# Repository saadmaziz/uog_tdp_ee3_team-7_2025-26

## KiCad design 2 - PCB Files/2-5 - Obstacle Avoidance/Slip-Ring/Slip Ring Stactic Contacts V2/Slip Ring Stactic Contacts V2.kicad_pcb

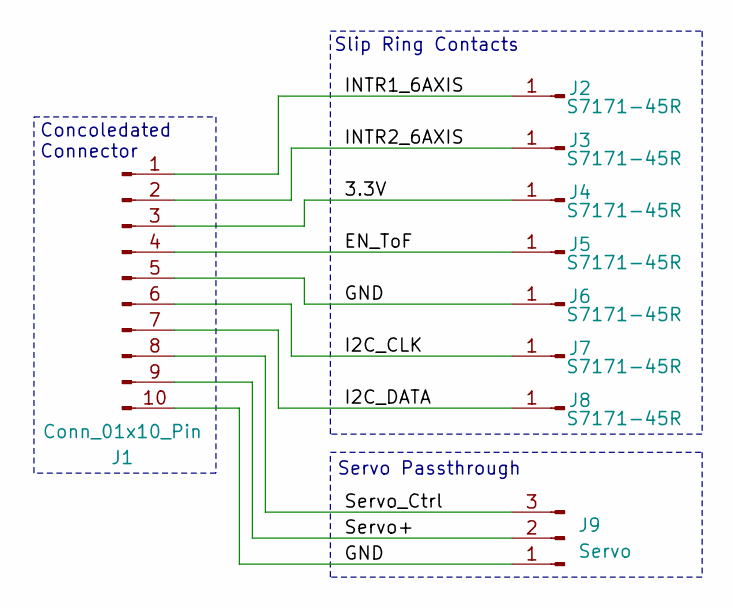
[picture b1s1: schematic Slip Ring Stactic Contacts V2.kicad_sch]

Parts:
J1: Conn_01x10_Pin; Molex_KK-254_AE-6410-10A_1x10_P2.54mm_Vertical
J2, J3, J4, J5, J6, J7, J8: S7171-45R; S717145R
J9: Servo; PinHeader_1x03_P2.54mm_Vertical

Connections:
/3.3V: J1.3, J4.1
/EN_ToF: J1.4, J5.1
/GND: J1.5, J1.10, J6.1, J9.1
/I2C_CLK: J1.6, J7.1
/I2C_DATA: J1.7, J8.1
/INTR1_6AXIS: J1.1, J2.1
/INTR2_6AXIS: J1.2, J3.1
/Servo+: J1.9, J9.2
/Servo_Ctrl: J1.8, J9.3

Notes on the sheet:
Slip Ring Contacts
Servo Passthrough
Concoledated Connector

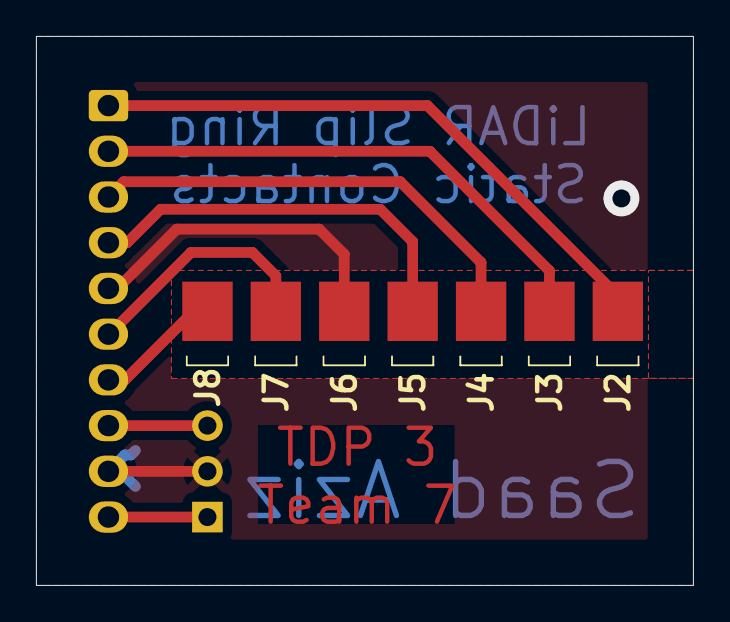
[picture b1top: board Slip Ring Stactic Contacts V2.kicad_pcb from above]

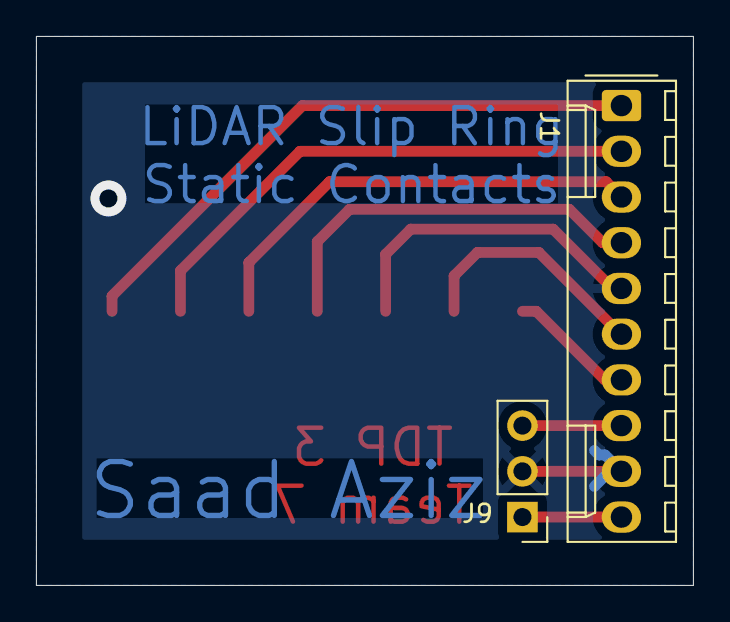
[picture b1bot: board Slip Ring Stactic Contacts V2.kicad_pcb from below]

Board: 2 copper layers, 36.5 x 30.5 mm, 9 parts (2 on the bottom side), 9 nets.

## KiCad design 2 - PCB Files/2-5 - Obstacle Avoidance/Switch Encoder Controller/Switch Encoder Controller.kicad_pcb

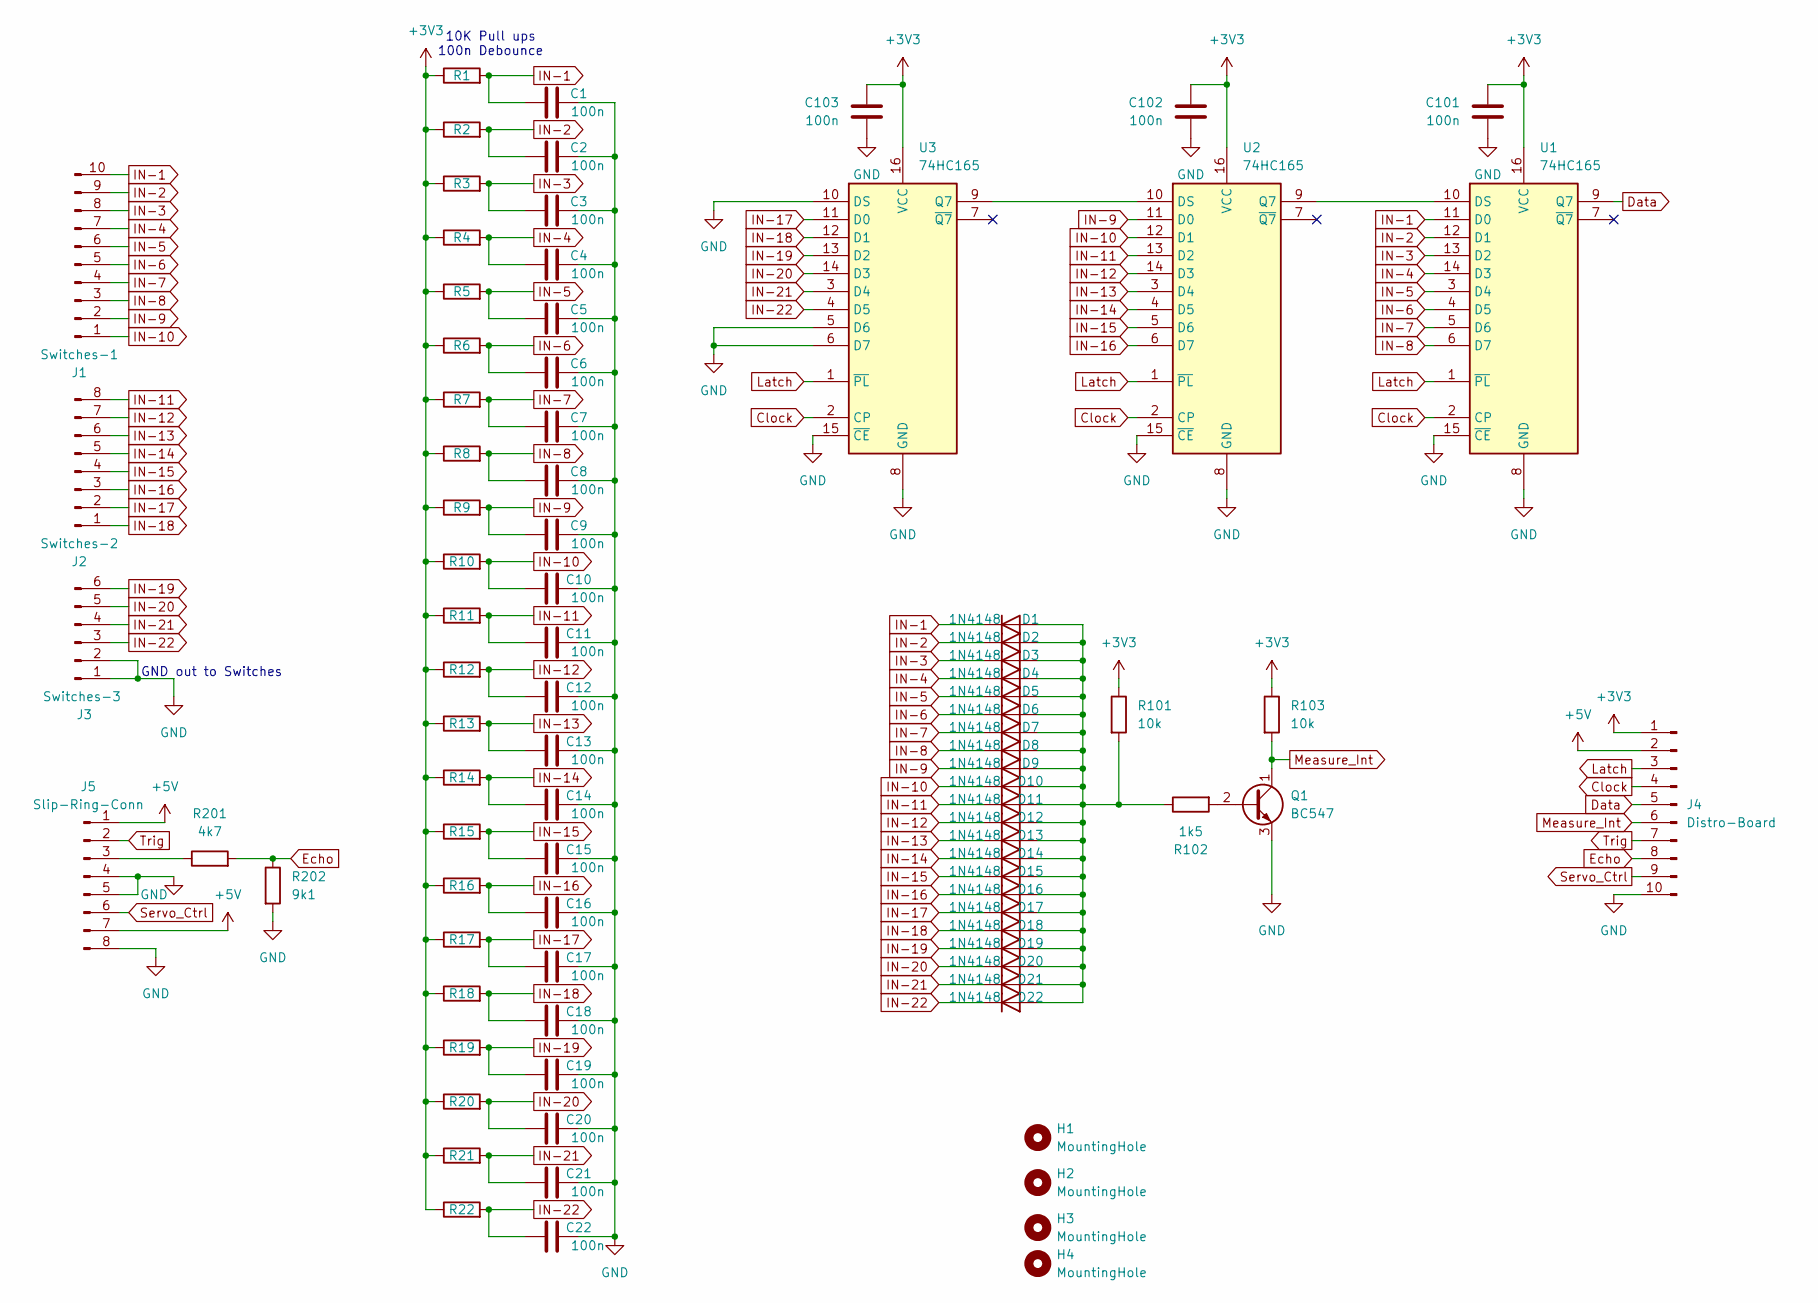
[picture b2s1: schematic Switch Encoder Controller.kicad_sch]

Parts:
C1, C2, C3, C4, C5, C6, C7, C8, C9, C10, C11, C12, C13, C14, C15, C16, C17, C18, C19, C20, C21, C22, C101, C102, C103: 100n; C_0805_2012Metric_Pad1.18x1.45mm_HandSolder
D1, D2, D3, D4, D5, D6, D7, D8, D9, D10, D11, D12, D13, D14, D15, D16, D17, D18, D19, D20, D21, D22: 1N4148; D_DO-35_SOD27_P7.62mm_Horizontal
H1, H2, H3, H4: MountingHole; MountingHole_3.2mm_M3_DIN965
J1: Switches-1; Molex_KK-254_AE-6410-10A_1x10_P2.54mm_Vertical
J2: Switches-2; Molex_KK-254_AE-6410-08A_1x08_P2.54mm_Vertical
J3: Switches-3; Molex_KK-254_AE-6410-06A_1x06_P2.54mm_Vertical
J4: Distro-Board; Molex_KK-254_AE-6410-10A_1x10_P2.54mm_Vertical
J5: Slip-Ring-Conn; Molex_KK-254_AE-6410-08A_1x08_P2.54mm_Vertical
Q1: BC547; TO-92_Inline_Wide
R1, R2, R3, R4, R5, R6, R7, R8, R9, R10, R11, R12, R13, R14, R15, R16, R17, R18, R19, R20, R21, R22, R101, R103: 10k; R_0805_2012Metric_Pad1.20x1.40mm_HandSolder
R102: 1k5; R_0805_2012Metric_Pad1.20x1.40mm_HandSolder
R201: 4k7; R_0805_2012Metric_Pad1.20x1.40mm_HandSolder
R202: 9k1; R_0805_2012Metric_Pad1.20x1.40mm_HandSolder
U1, U2, U3: 74HC165; DIP-16_W7.62mm_Socket_LongPads

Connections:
+3V3: C101.1, C102.1, C103.1, J4.1, R1.1, R2.1, R3.1, R4.1, R5.1, R6.1, R7.1, R8.1, R9.1, R10.1, R11.1, R12.1, R13.1, R14.1, R15.1, R16.1, R17.1, R18.1, R19.1, R20.1, R21.1, R22.1, R101.1, R103.1, U1.16 (VCC), U2.16 (VCC), U3.16 (VCC)
+5V: J4.2, J5.1, J5.7
Clock: J4.4, U1.2 (CP), U2.2 (CP), U3.2 (CP)
Data: J4.5, U1.9 (Q7)
Echo: J4.8, R201.2, R202.1
GND: C1.2, C2.2, C3.2, C4.2, C5.2, C6.2, C7.2, C8.2, C9.2, C10.2, C11.2, C12.2, C13.2, C14.2, C15.2, C16.2, C17.2, C18.2, C19.2, C20.2, C21.2, C22.2, C101.2, C102.2, C103.2, J3.1, J3.2, J4.10, J5.4, J5.5, J5.8, Q1.3 (E), R202.2, U1.8 (GND), U1.15 (~CE), U2.8 (GND), U2.15 (~CE), U3.5 (D6), U3.6 (D7), U3.8 (GND), U3.10 (DS), U3.15 (~CE)
IN-1: C1.1, D1.1 (K), J1.10, R1.2, U1.11 (D0)
IN-2: C2.1, D2.1 (K), J1.9, R2.2, U1.12 (D1)
IN-3: C3.1, D3.1 (K), J1.8, R3.2, U1.13 (D2)
IN-4: C4.1, D4.1 (K), J1.7, R4.2, U1.14 (D3)
IN-5: C5.1, D5.1 (K), J1.6, R5.2, U1.3 (D4)
IN-6: C6.1, D6.1 (K), J1.5, R6.2, U1.4 (D5)
IN-7: C7.1, D7.1 (K), J1.4, R7.2, U1.5 (D6)
IN-8: C8.1, D8.1 (K), J1.3, R8.2, U1.6 (D7)
IN-9: C9.1, D9.1 (K), J1.2, R9.2, U2.11 (D0)
IN-10: C10.1, D10.1 (K), J1.1, R10.2, U2.12 (D1)
IN-11: C11.1, D11.1 (K), J2.8, R11.2, U2.13 (D2)
IN-12: C12.1, D12.1 (K), J2.7, R12.2, U2.14 (D3)
IN-13: C13.1, D13.1 (K), J2.6, R13.2, U2.3 (D4)
IN-14: C14.1, D14.1 (K), J2.5, R14.2, U2.4 (D5)
IN-15: C15.1, D15.1 (K), J2.4, R15.2, U2.5 (D6)
IN-16: C16.1, D16.1 (K), J2.3, R16.2, U2.6 (D7)
IN-17: C17.1, D17.1 (K), J2.2, R17.2, U3.11 (D0)
IN-18: C18.1, D18.1 (K), J2.1, R18.2, U3.12 (D1)
IN-19: C19.1, D19.1 (K), J3.6, R19.2, U3.13 (D2)
IN-20: C20.1, D20.1 (K), J3.5, R20.2, U3.14 (D3)
IN-21: C21.1, D21.1 (K), J3.4, R21.2, U3.3 (D4)
IN-22: C22.1, D22.1 (K), J3.3, R22.2, U3.4 (D5)
Latch: J4.3, U1.1 (~PL), U2.1 (~PL), U3.1 (~PL)
Measure_Int: J4.6, Q1.1 (C), R103.2
unnamed: D1.2 (A), D2.2 (A), D3.2 (A), D4.2 (A), D5.2 (A), D6.2 (A), D7.2 (A), D8.2 (A), D9.2 (A), D10.2 (A), D11.2 (A), D12.2 (A), D13.2 (A), D14.2 (A), D15.2 (A), D16.2 (A), D17.2 (A), D18.2 (A), D19.2 (A), D20.2 (A), D21.2 (A), D22.2 (A), R101.2, R102.1
unnamed: J5.3, R201.1
unnamed: Q1.2 (B), R102.2
unnamed: U1.10 (DS), U2.9 (Q7)
unnamed: U2.10 (DS), U3.9 (Q7)
Servo_Ctrl: J4.9, J5.6
Trig: J4.7, J5.2

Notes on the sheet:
GND out to Switches
10K Pull ups 100n Debounce

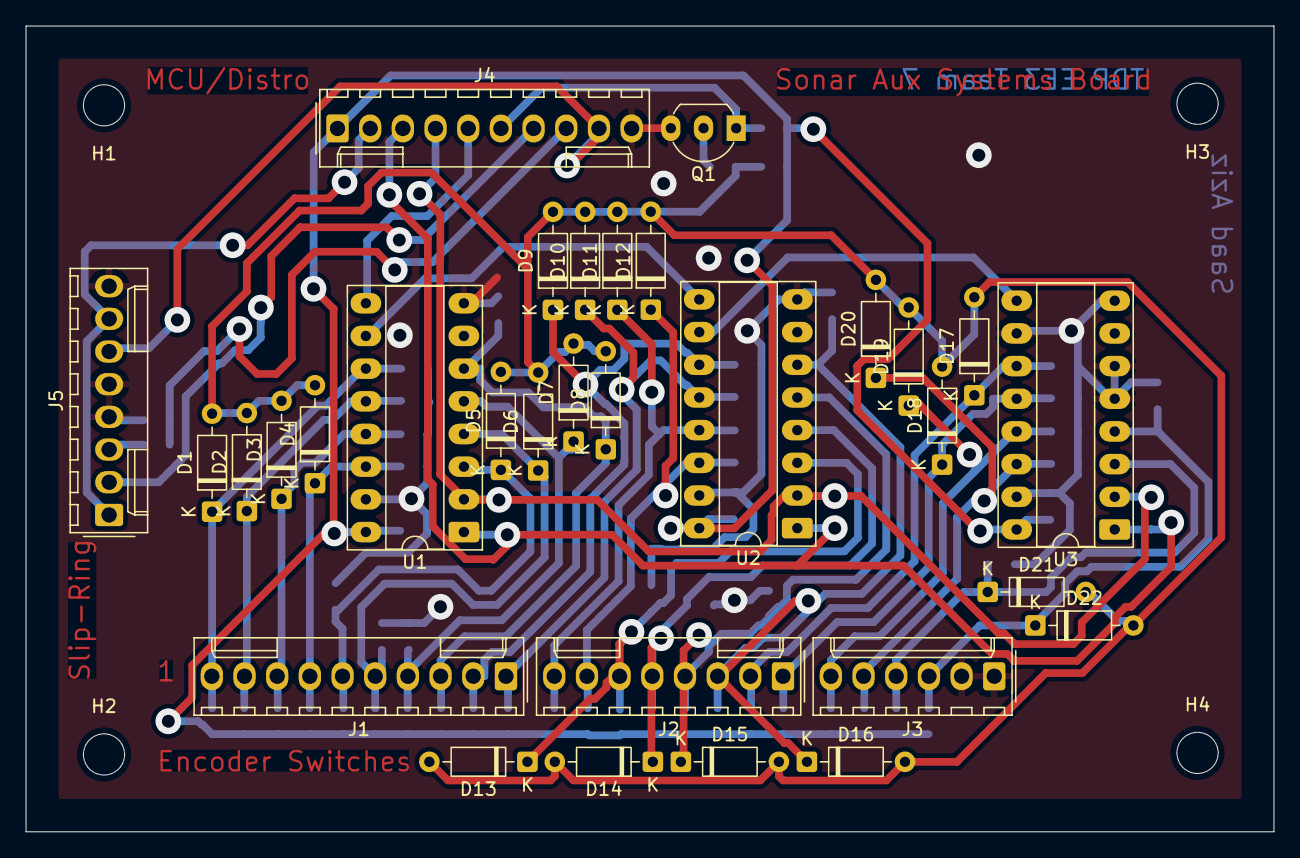
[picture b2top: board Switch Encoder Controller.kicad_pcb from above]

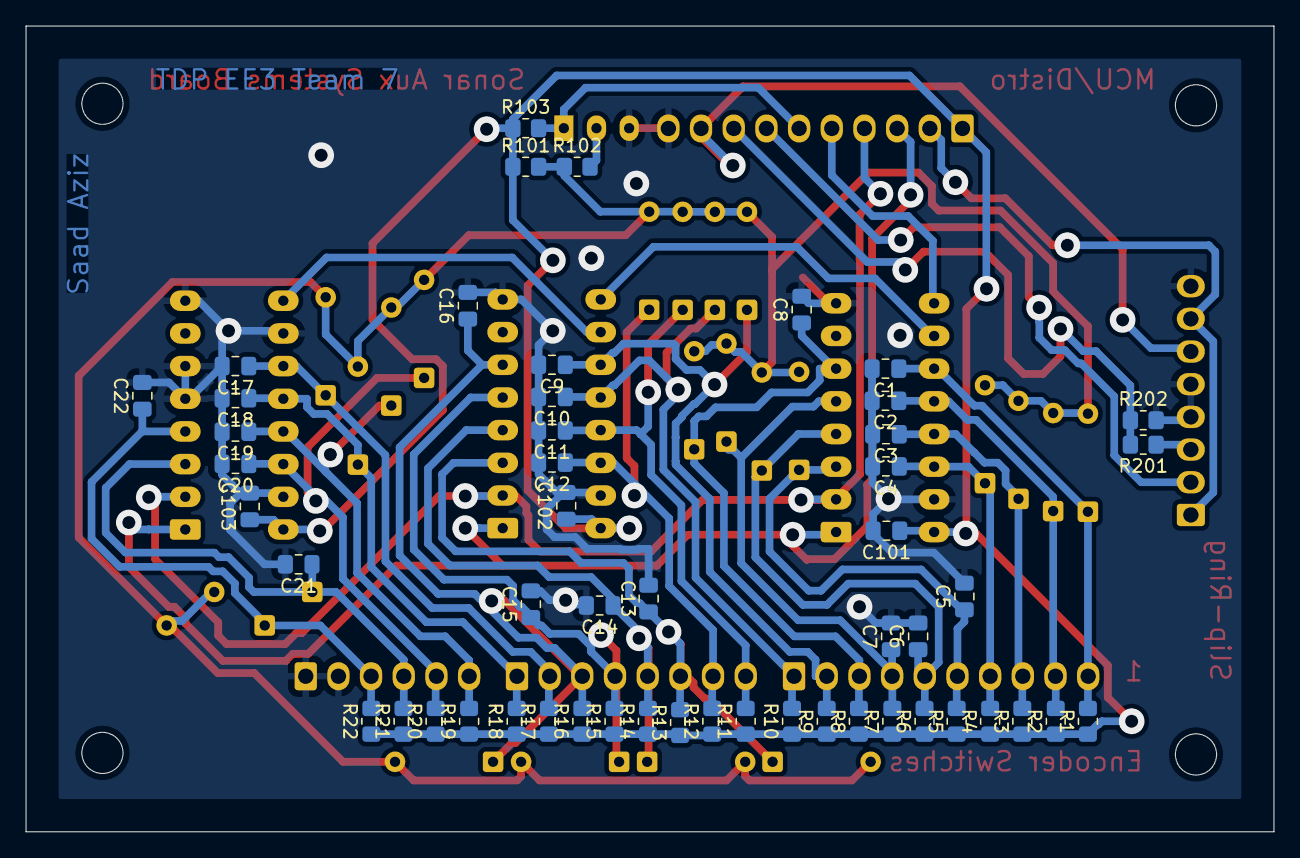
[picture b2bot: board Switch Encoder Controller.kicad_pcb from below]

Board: 2 copper layers, 97.0 x 62.6 mm, 87 parts (52 on the bottom side), 37 nets.

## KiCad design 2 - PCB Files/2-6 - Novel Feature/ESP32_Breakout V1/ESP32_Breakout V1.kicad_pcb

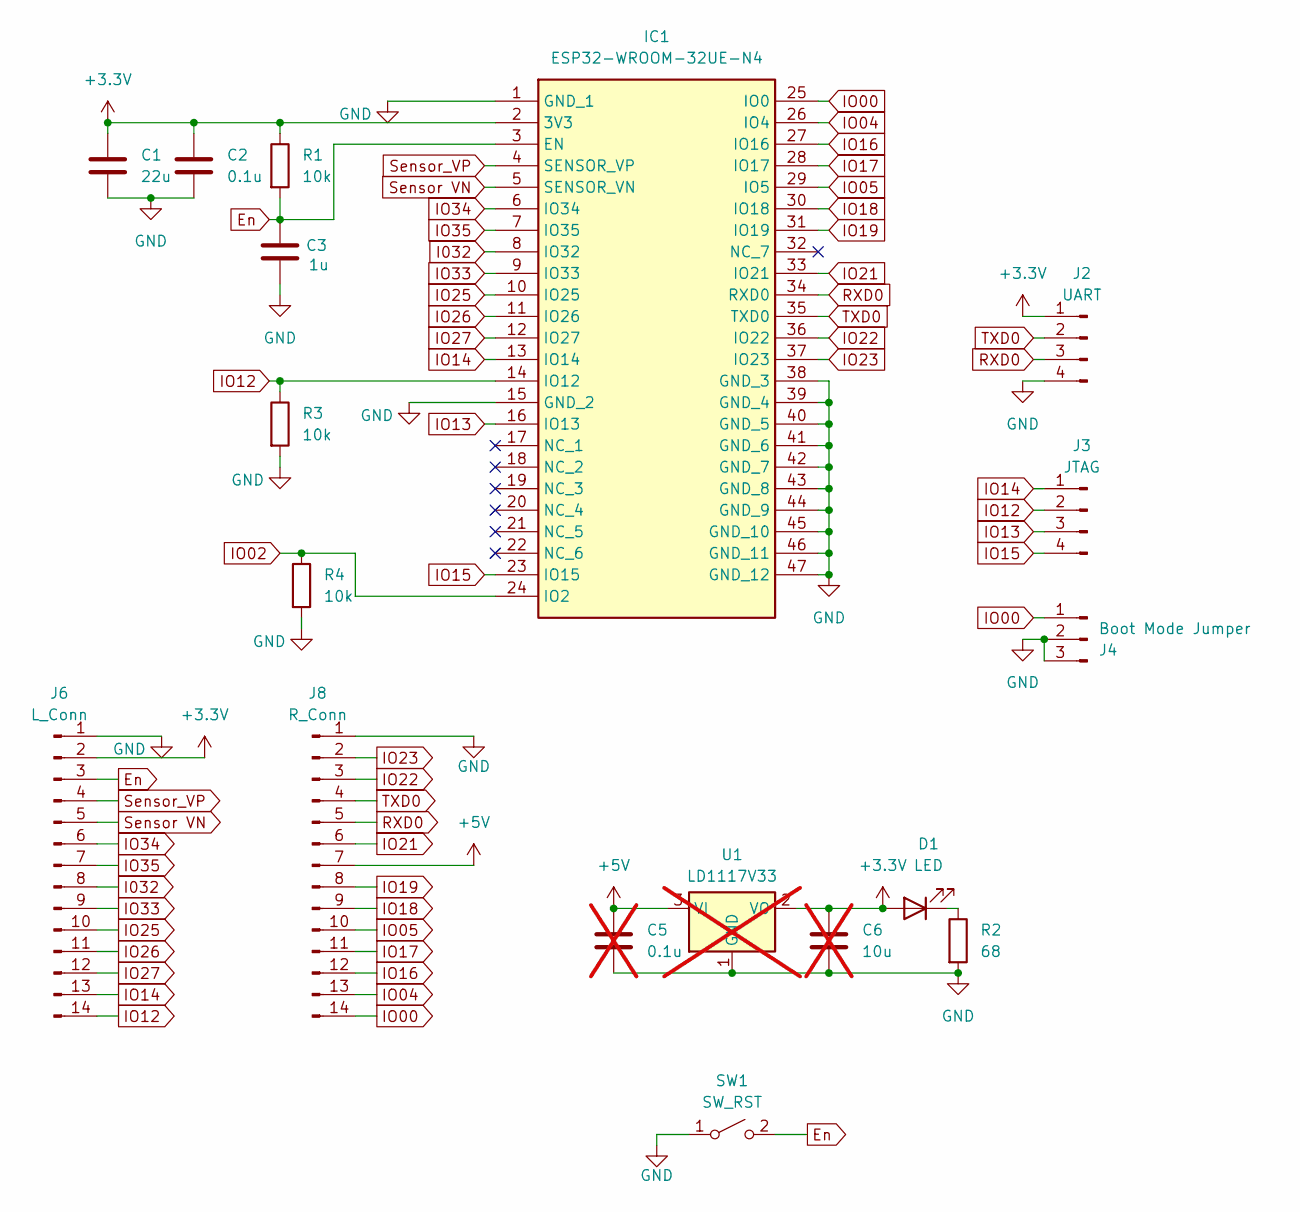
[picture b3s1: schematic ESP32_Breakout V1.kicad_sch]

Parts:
C1: 22u; CP_Elec_6.3x7.7
C2: 0.1u; C_0805_2012Metric
C3: 1u; C_0805_2012Metric
C5: 0.1u; C_0805_2012Metric; not fitted
C6: 10u; CP_Elec_6.3x7.7; not fitted
D1: LED; LED_0805_2012Metric_Pad1.15x1.40mm_HandSolder
IC1: ESP32-WROOM-32UE-N4; ESP32WROOM32UEN4; Manufacturer_Part_Number ESP32-WROOM-32UE-N4; Mouser Part Number 356-ESP32WRM32UE32UH
J2: UART; PinHeader_1x04_P2.54mm_Vertical
J3: JTAG; PinHeader_1x04_P2.54mm_Vertical
J4: Boot Mode Jumper; PinHeader_1x03_P2.54mm_Vertical
J6: L_Conn; PinHeader_1x14_P2.54mm_Vertical
J8: R_Conn; PinHeader_1x14_P2.54mm_Vertical
R1, R3, R4: 10k; R_0805_2012Metric_Pad1.20x1.40mm_HandSolder
R2: 68; R_0805_2012Metric_Pad1.20x1.40mm_HandSolder
SW1: SW_RST; Switch_SPST_2P
U1: LD1117V33; TO-220-3_Horizontal_TabUp; not fitted

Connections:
+3.3V: C1.1, C2.1, C6.1, D1.2 (A), IC1.2 (3V3), J2.1, J6.2, R1.1, U1.2 (VO)
+5V: C5.1, J8.7, U1.3 (VI)
En: C3.2, IC1.3 (EN), J6.3, R1.2, SW1.2 (B)
GND: C1.2, C2.2, C3.1, C5.2, C6.2, IC1.1 (GND_1), IC1.15 (GND_2), IC1.38 (GND_3), IC1.39 (GND_4), IC1.40 (GND_5), IC1.41 (GND_6), IC1.42 (GND_7), IC1.43 (GND_8), IC1.44 (GND_9), IC1.45 (GND_10), IC1.46 (GND_11), IC1.47 (GND_12), J2.4, J4.2, J4.3, J6.1, J8.1, R2.2, R3.2, R4.2, SW1.1 (A), U1.1 (GND)
I032: IC1.8 (IO32), J6.8
IO00: IC1.25 (IO0), J4.1, J8.14
IO02: IC1.24 (IO2), R4.1
IO04: IC1.26 (IO4), J8.13
IO05: IC1.29 (IO5), J8.10
IO12: IC1.14 (IO12), J3.2, J6.14, R3.1
IO13: IC1.16 (IO13), J3.3
IO14: IC1.13 (IO14), J3.1, J6.13
IO15: IC1.23 (IO15), J3.4
IO16: IC1.27 (IO16), J8.12
IO17: IC1.28 (IO17), J8.11
IO18: IC1.30 (IO18), J8.9
IO19: IC1.31 (IO19), J8.8
IO21: IC1.33 (IO21), J8.6
IO22: IC1.36 (IO22), J8.3
IO23: IC1.37 (IO23), J8.2
IO25: IC1.10 (IO25), J6.10
IO26: IC1.11 (IO26), J6.11
IO27: IC1.12 (IO27), J6.12
IO33: IC1.9 (IO33), J6.9
IO34: IC1.6 (IO34), J6.6
IO35: IC1.7 (IO35), J6.7
unnamed: D1.1 (K), R2.1
RXD0: IC1.34 (RXD0), J2.3, J8.5
Sensor VN: IC1.5 (SENSOR_VN), J6.5
Sensor_VP: IC1.4 (SENSOR_VP), J6.4
TXD0: IC1.35 (TXD0), J2.2, J8.4

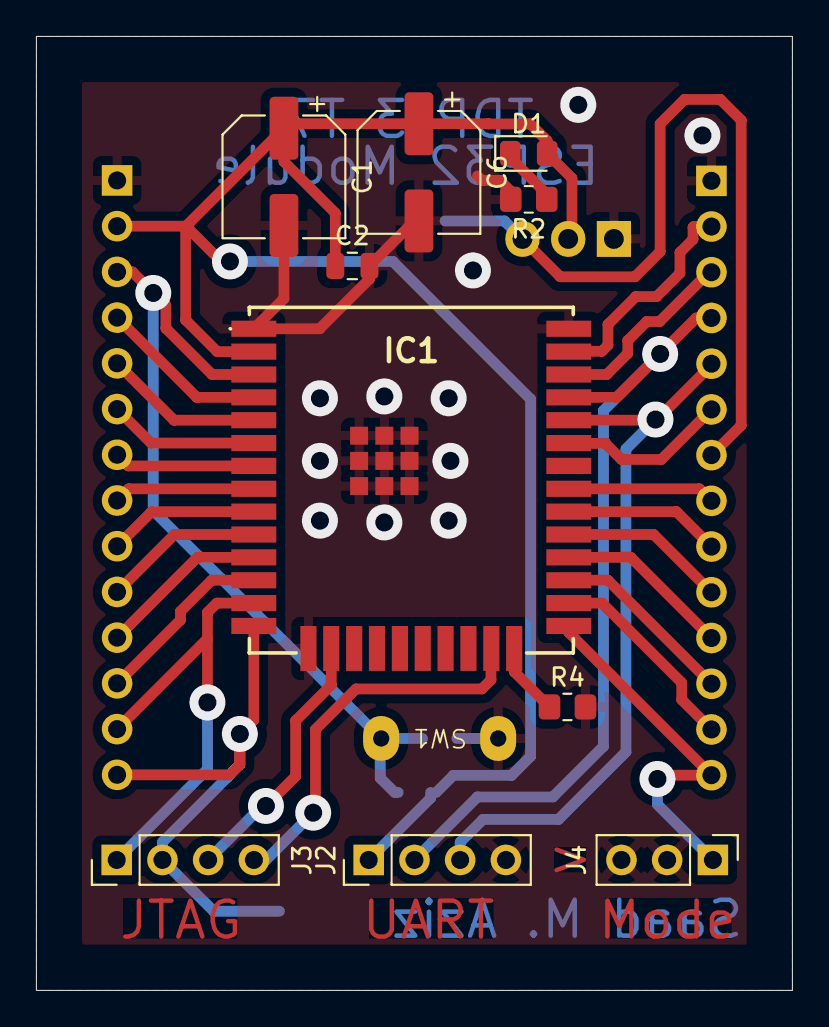
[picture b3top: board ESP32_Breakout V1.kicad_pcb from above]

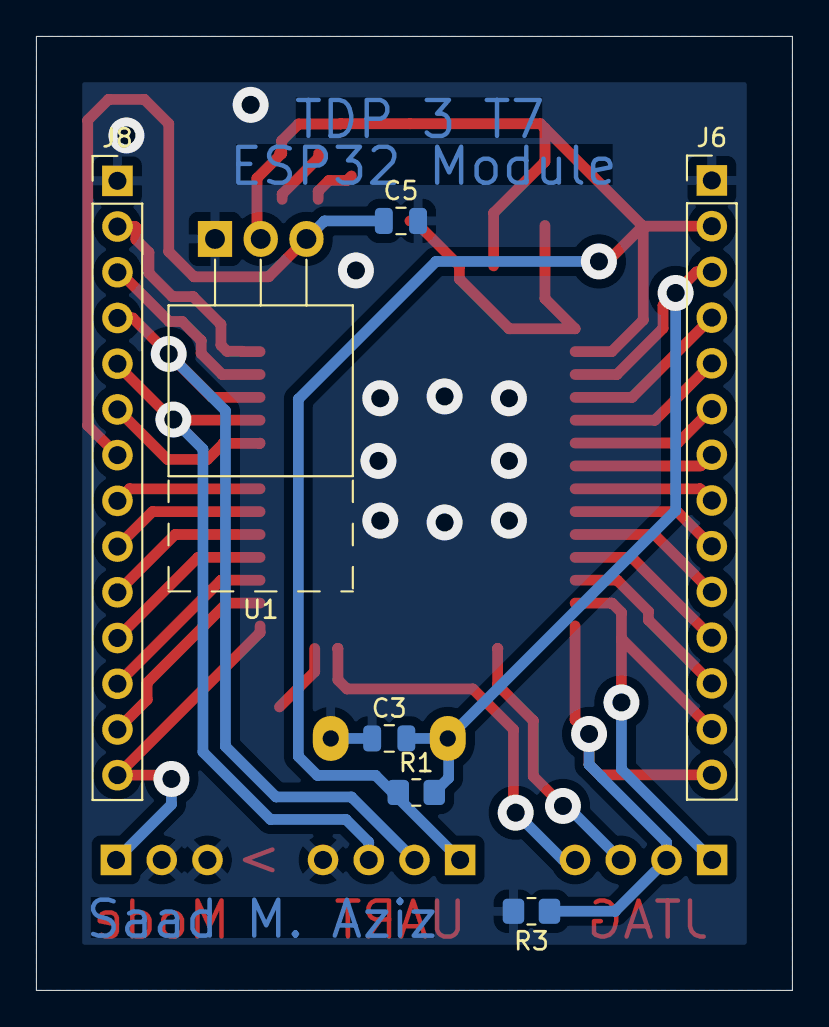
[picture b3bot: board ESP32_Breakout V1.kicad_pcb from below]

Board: 2 copper layers, 42.0 x 53.0 mm, 18 parts (7 on the bottom side), 31 nets.

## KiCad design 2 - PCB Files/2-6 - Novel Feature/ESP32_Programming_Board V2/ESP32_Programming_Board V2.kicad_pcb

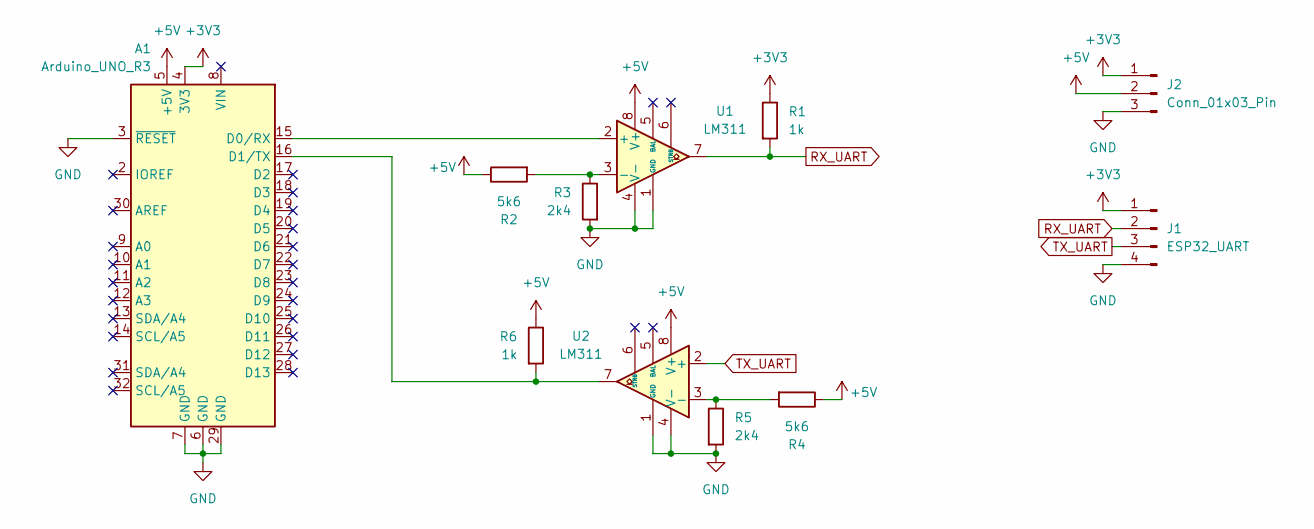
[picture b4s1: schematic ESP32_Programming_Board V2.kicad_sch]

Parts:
A1: Arduino_UNO_R3
J1: ESP32_UART; PinSocket_1x04_P2.54mm_Vertical
J2: Conn_01x03_Pin; PinSocket_1x03_P2.54mm_Vertical
R1, R6: 1k; R_0805_2012Metric_Pad1.20x1.40mm_HandSolder
R2, R4: 5k6; R_0805_2012Metric_Pad1.20x1.40mm_HandSolder
R3, R5: 2k4; R_0805_2012Metric_Pad1.20x1.40mm_HandSolder
U1, U2: LM311; DIP-8_W7.62mm_LongPads

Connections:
+3V3: A1.4 (3V3), J1.1, J2.1, R1.1
+5V: A1.5 (+5V), J2.2, R2.1, R4.1, R6.1, U1.8 (V+), U2.8 (V+)
GND: A1.3 (~RESET), A1.6 (GND), A1.7 (GND), A1.29 (GND), J1.4, J2.3, R3.2, R5.2, U1.1 (GND), U1.4 (V-), U2.1 (GND), U2.4 (V-)
unnamed: A1.15 (D0/RX), U1.2 (+)
unnamed: A1.16 (D1/TX), R6.2, U2.7
unnamed: R2.2, R3.1, U1.3 (-)
unnamed: R4.2, R5.1, U2.3 (-)
RX_UART: J1.2, R1.2, U1.7
TX_UART: J1.3, U2.2 (+)

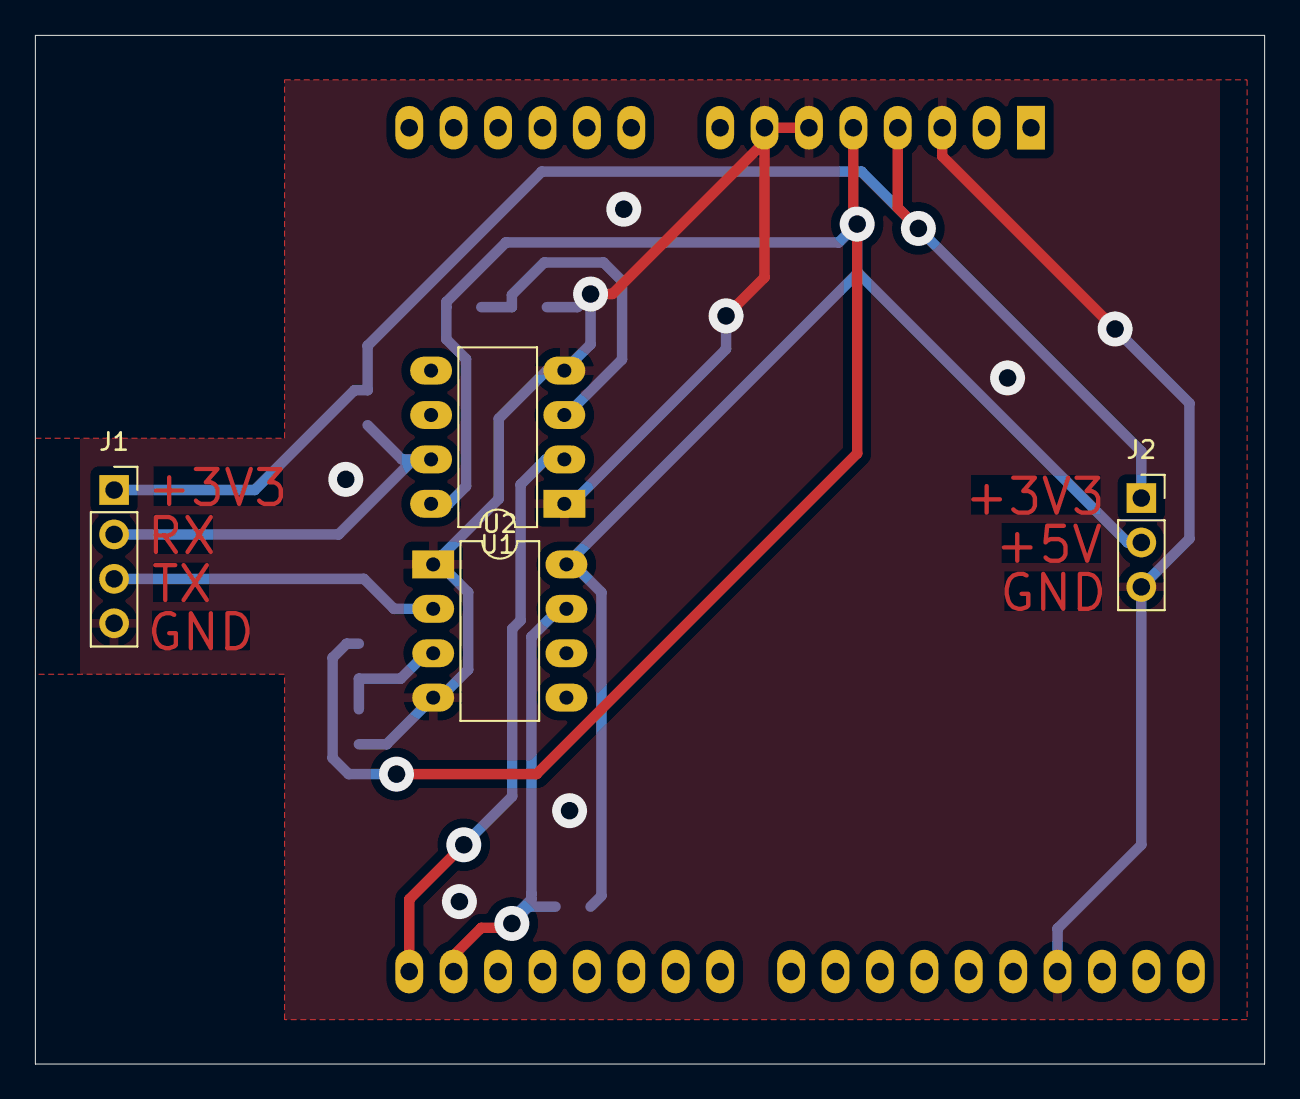
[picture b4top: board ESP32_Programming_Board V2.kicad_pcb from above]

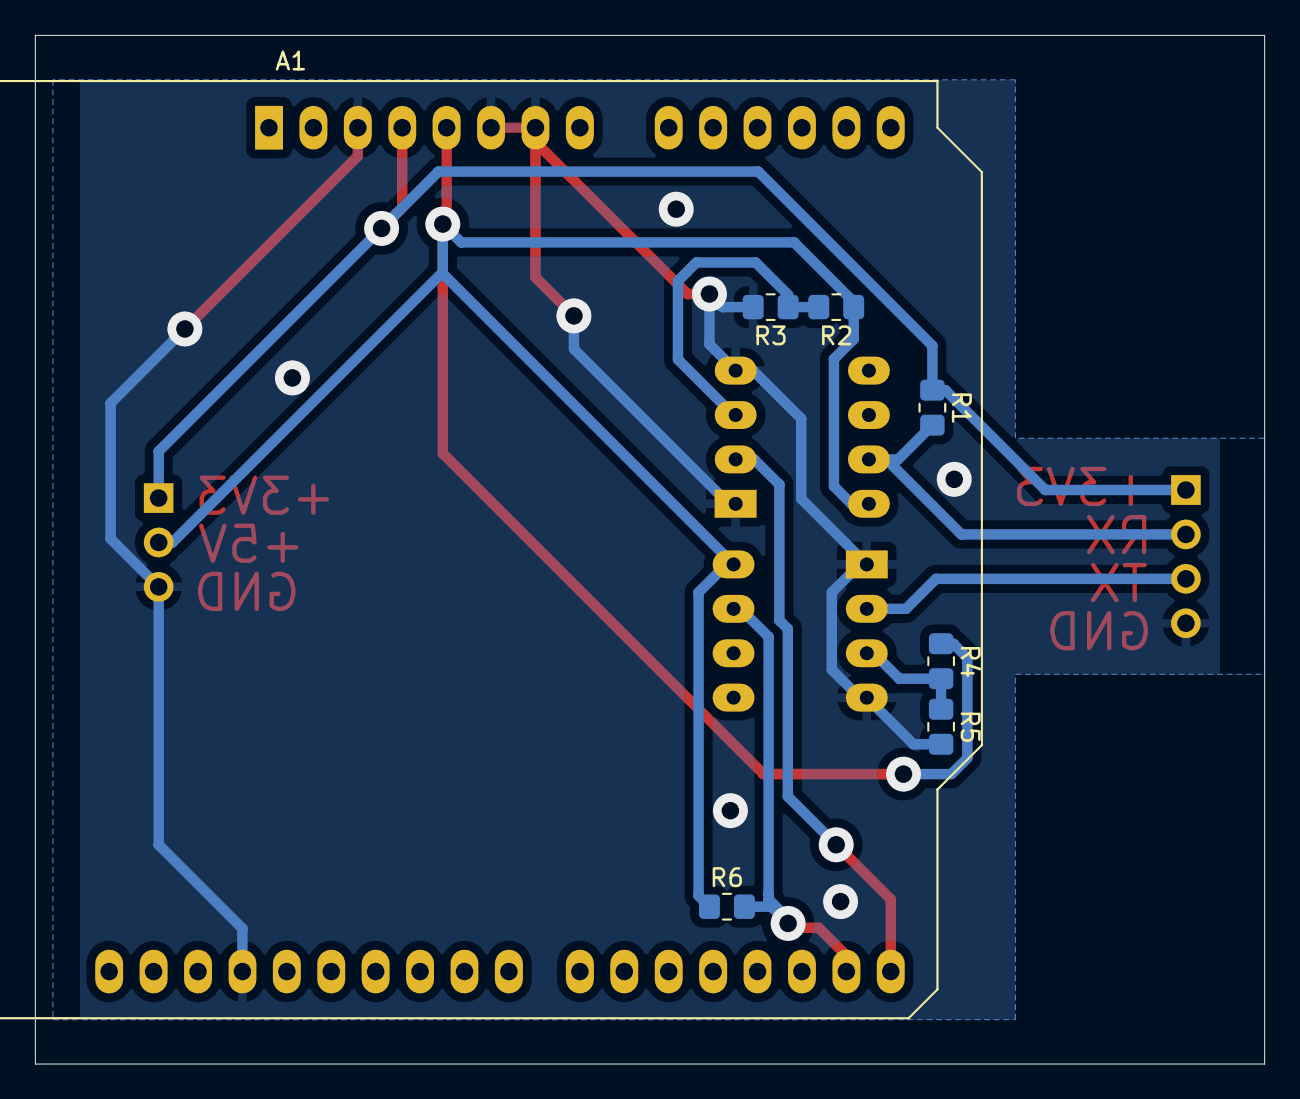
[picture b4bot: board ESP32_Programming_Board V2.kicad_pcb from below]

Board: 2 copper layers, 70.3 x 58.8 mm, 11 parts (7 on the bottom side), 9 nets.

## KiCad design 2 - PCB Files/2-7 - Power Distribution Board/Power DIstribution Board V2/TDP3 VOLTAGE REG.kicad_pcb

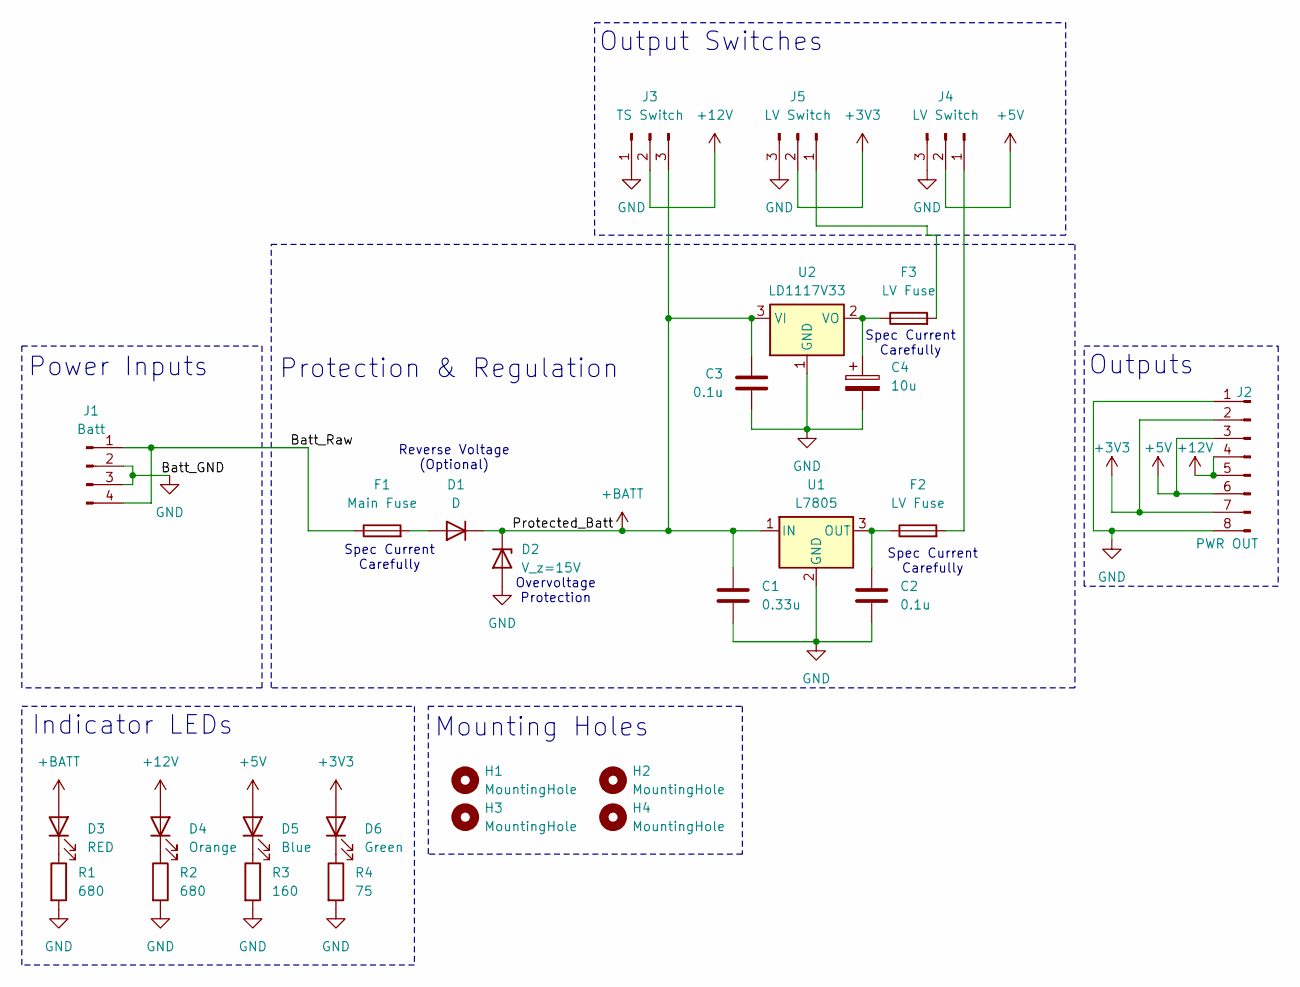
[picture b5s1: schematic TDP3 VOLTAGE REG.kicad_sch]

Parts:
C1: 0.33u; C_0805_2012Metric_Pad1.18x1.45mm_HandSolder
C2, C3: 0.1u; C_0805_2012Metric_Pad1.18x1.45mm_HandSolder
C4: 10u; CP_Radial_D5.0mm_P2.00mm
D1: D; D_DO-35_SOD27_P7.62mm_Horizontal
D2: V_z=15V; D_DO-35_SOD27_P7.62mm_Horizontal
D3: RED; D_0805_2012Metric_Pad1.15x1.40mm_HandSolder
D4: Orange; D_0805_2012Metric_Pad1.15x1.40mm_HandSolder
D5: Blue; D_0805_2012Metric_Pad1.15x1.40mm_HandSolder
D6: Green; D_0805_2012Metric_Pad1.15x1.40mm_HandSolder
F1: Main Fuse; CamdenBoss CFH02_W Fuse Holder
F2, F3: LV Fuse; CamdenBoss CFH02_W Fuse Holder
H1, H2, H3, H4: MountingHole; MountingHole_3.2mm_M3
J1: Batt; Molex_KK-254_AE-6410-04A_1x04_P2.54mm_Vertical
J2: PWR OUT; Molex_KK-254_AE-6410-08A_1x08_P2.54mm_Vertical
J3: TS Switch; Molex_KK-254_AE-6410-03A_1x03_P2.54mm_Vertical
J4, J5: LV Switch; Molex_KK-254_AE-6410-03A_1x03_P2.54mm_Vertical
R1, R2: 680; R_0805_2012Metric_Pad1.20x1.40mm_HandSolder
R3: 160; R_0805_2012Metric_Pad1.20x1.40mm_HandSolder
R4: 75; R_0805_2012Metric_Pad1.20x1.40mm_HandSolder
U1: L7805; TO-220-3_Vertical
U2: LD1117V33; TO-220-3_Vertical

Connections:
+3V3: D6.2 (A), J2.2, J2.7, J5.2
+5V: D5.2 (A), J2.3, J2.6, J4.2
+12V: D4.2 (A), J2.4, J2.5, J3.2
+BATT: C1.1, C3.1, D1.1 (K), D2.1 (K), D3.2 (A), J3.3, U1.1 (IN), U2.3 (VI)
/Batt_Raw: F1.1, J1.1, J1.4
GND: C1.2, C2.2, C3.2, C4.2, D2.2 (A), J1.2, J1.3, J2.1, J2.8, J3.1, J4.3, J5.3, R1.2, R2.2, R3.2, R4.2, U1.2 (GND), U2.1 (GND)
unnamed: D1.2 (A), F1.2
unnamed: D3.1 (K), R1.1
unnamed: D4.1 (K), R2.1
unnamed: D5.1 (K), R3.1
unnamed: D6.1 (K), R4.1
unnamed: F2.2, J4.1
unnamed: F3.2, J5.1
unnamed: C2.1, F2.1, U1.3 (OUT)
unnamed: C4.1, F3.1, U2.2 (VO)

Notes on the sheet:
Spec Current Carefully
Output Switches
Mounting Holes
Protection & Regulation
Outputs
Indicator LEDs
Overvoltage Protection
Power Inputs
Reverse Voltage (Optional)

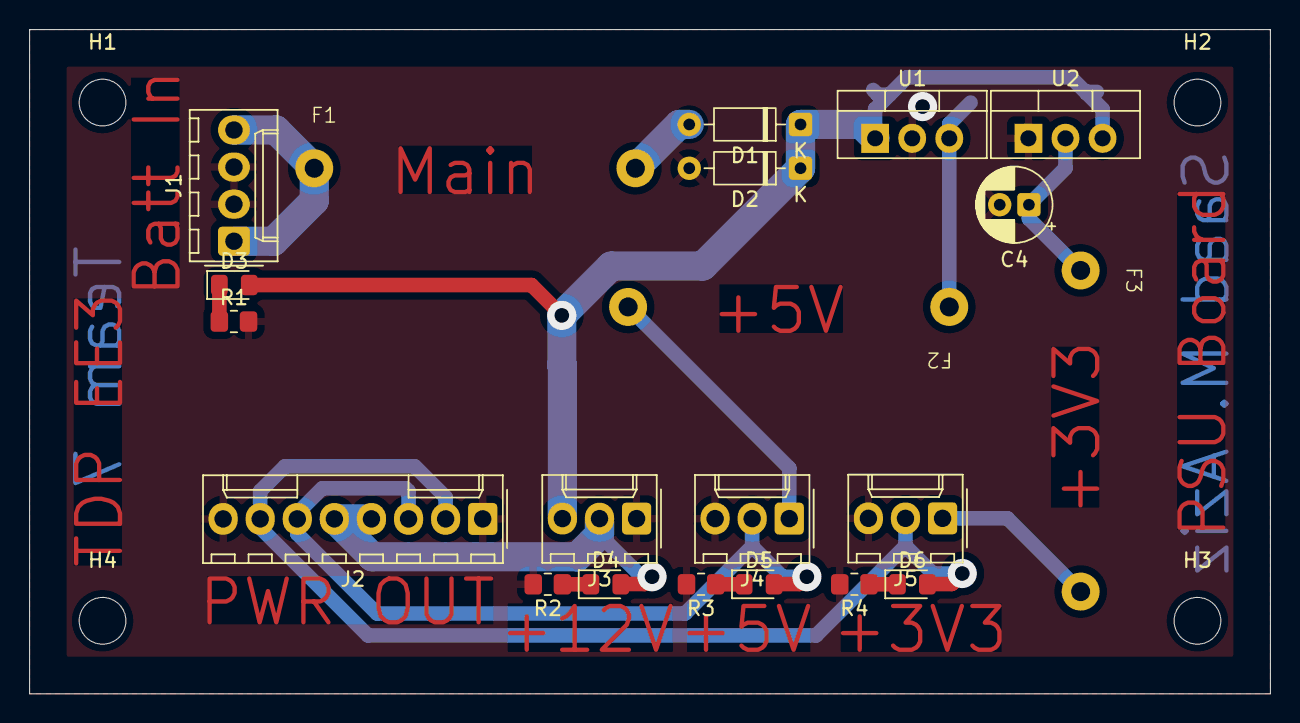
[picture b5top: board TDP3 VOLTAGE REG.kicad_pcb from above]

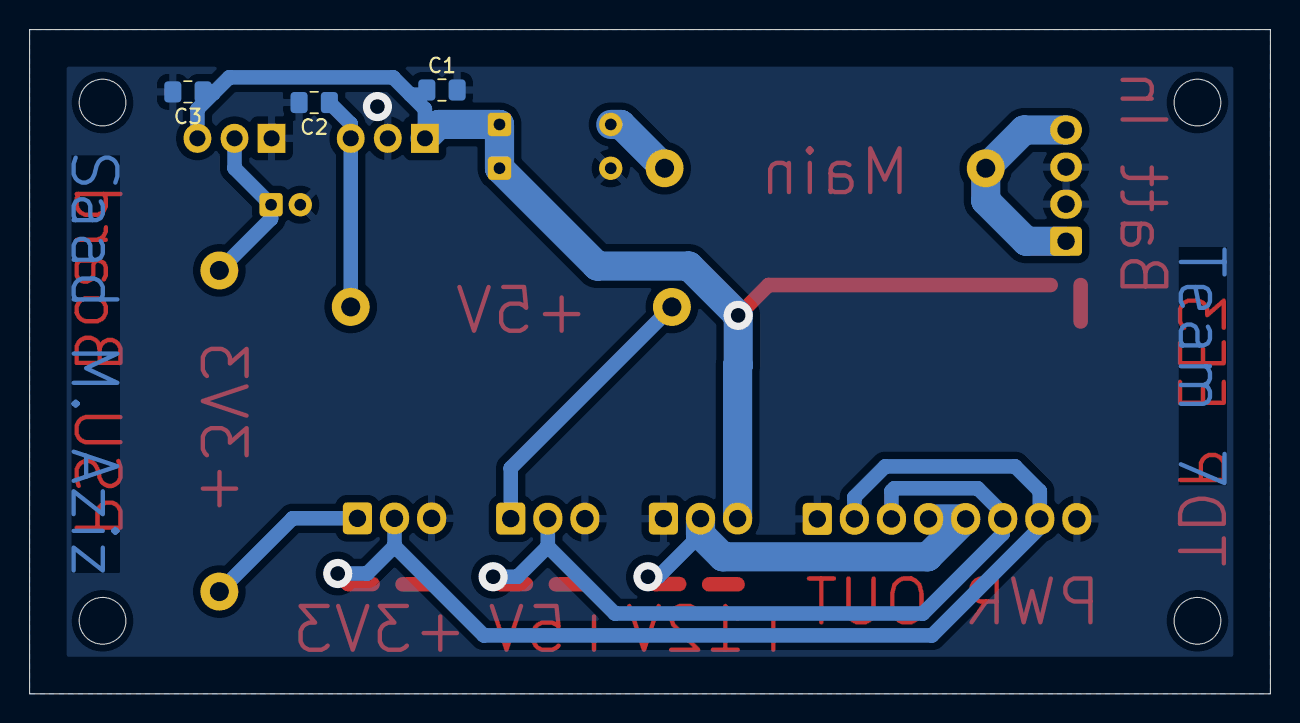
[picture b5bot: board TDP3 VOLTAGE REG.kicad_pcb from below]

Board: 2 copper layers, 85.0 x 45.5 mm, 28 parts (3 on the bottom side), 15 nets.

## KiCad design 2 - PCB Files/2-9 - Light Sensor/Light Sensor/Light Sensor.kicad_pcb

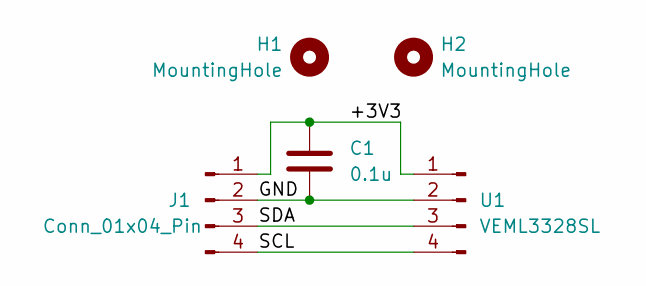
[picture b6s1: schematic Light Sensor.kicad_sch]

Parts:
C1: 0.1u; C_0805_2012Metric_Pad1.18x1.45mm_HandSolder
H1, H2: MountingHole; MountingHole_3.2mm_M3
J1: Conn_01x04_Pin; Molex_KK-254_AE-6410-04A_1x04_P2.54mm_Vertical
U1: VEML3328SL

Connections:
/+3V3: C1.1, J1.1, U1.1
/GND: C1.2, J1.2, U1.2
/SCL: J1.4, U1.4
/SDA: J1.3, U1.3

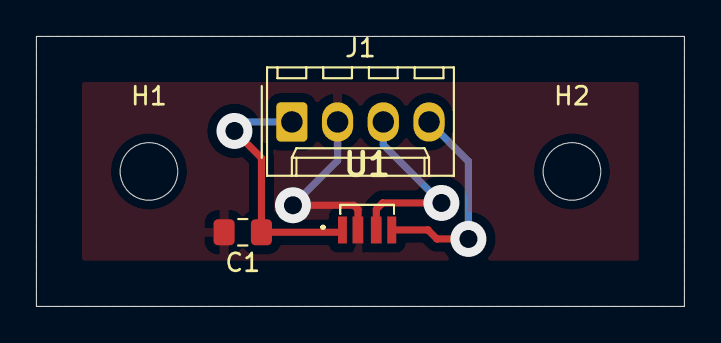
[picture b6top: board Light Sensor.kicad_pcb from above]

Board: 2 copper layers, 36.0 x 15.0 mm, 5 parts (0 on the bottom side), 4 nets.
